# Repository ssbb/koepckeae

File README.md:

# koepckeae

koepckeae is a 34-key unibody split keyboard higihly inspired by Pete Johanson's [Zaphod Lite](https://gitlab.com/lpgalaxy/zaphod/-/tree/main), featuring hotswap support, splay, and spaced out thumbs.

## BOM

| Qty | Name                                                        | Source                                                                                                             |
|-----|-------------------------------------------------------------|--------------------------------------------------------------------------------------------------------------------|
| 1   | PCB                                                         | [gerbers](pcb/choc/koepckeae_gerbers.zip)                                                                          |
| 1   | XIAO nRF52840                                               | [Digikey](https://www.digikey.com/en/products/detail/seeed-technology-co-ltd/102010448/16652893)                   |
| 1   | 74HC595D shift register (SOIC-16)                           | [LCSC](https://www.lcsc.com/product-detail/Shifting-Register_Nexperia-74HC595D-118_C5947.html)                     |
| 1   | PCM12 power switch                                          | [LCSC](https://www.lcsc.com/product-detail/Slide-Switches_C-K-PCM12SMTR_C221841.html)                              |
| 1   | Panasonic EVQPUC02K reset button                            | [LCSC](https://www.lcsc.com/product-detail/_PANASONIC-_C79174.html)                                                |
| 2   | 1x1 Mill-Max Spring Loaded Header (0906-2-15-20-75-14-11-0) | [Digikey](https://www.digikey.com/en/products/detail/mill-max-manufacturing-corp/0906-2-15-20-75-14-11-0/1147050)  |
| 2   | 1x7 Mill-Max Header (310-43-107-41-001000)                  | [Digikey](https://www.digikey.com/en/products/detail/mill-max-manufacturing-corp/310-43-107-41-001000/1212181)     |
| 1   | JST PH-2.0 battery socket                                   | [LCSC](https://www.lcsc.com/product-detail/Wire-To-Board-Wire-To-Wire-Connector_JST-S2B-PH-K-S-LF-SN_C173752.html) |
| 1   | 702025 300 mAh battery                                      |                                                                                                                    |
| 34  | 1N4148W diode                                               | [LCSC](https://www.lcsc.com/product-detail/Switching-Diode_MDD-Microdiode-Electronics-1N4148W_C84367.html)         |
| 34  | Kailh Choc hotswap sockets                                  | [Aliexpress](https://aliexpress.com/item/33023283633.html?sku_id=10000000883911874)                                |

Max battery dimensions are 29mm x 21mm x 8mm. Ideally get a battery with JST connector but double check polarity on PCB.

### Plate case

| Qty | Name         | Source                                                             |
|-----|--------------|--------------------------------------------------------------------|
| 1   | Bottom Plate | [gerbers](mechanical/bottom-plate/bottom_plate_gerbers.zip)        |
| 8   | Solder Nuts  | [LCSC](https://www.lcsc.com/product-detail/_Sinhoo-_C2916384.html) |
| 8   | M2x5 screws  |                                                                    |

### Display

| Qty | Name                                                     | Source                                                                                                         |
|-----|----------------------------------------------------------|----------------------------------------------------------------------------------------------------------------|
| 1   | Adafruit Sharp Memory Display                            | [Adafruit](https://www.adafruit.com/product/3502)                                                              |
| 1   | 1x5 Mill-Max Spring Loaded Header (825-22-005-10-001101) | [Digikey](https://www.digikey.com/en/products/detail/mill-max-manufacturing-corp/825-22-005-10-001101/6149696) |
| 4   | M2.5x6 male-female nylon standoff                        | [Aliexpress](https://aliexpress.com/item/32871403400.html?sku_id=10000002420611426)                            |
| 4   | M2.5 nylon nut                                           | [Aliexpress](https://aliexpress.com/item/32868992270.html?sku_id=10000010058105677)                            |
| 4   | M2.5x6 nylon screw                                       | [Aliexpress](https://aliexpress.com/item/32870030598.html?sku_id=10000002668418327)                            |

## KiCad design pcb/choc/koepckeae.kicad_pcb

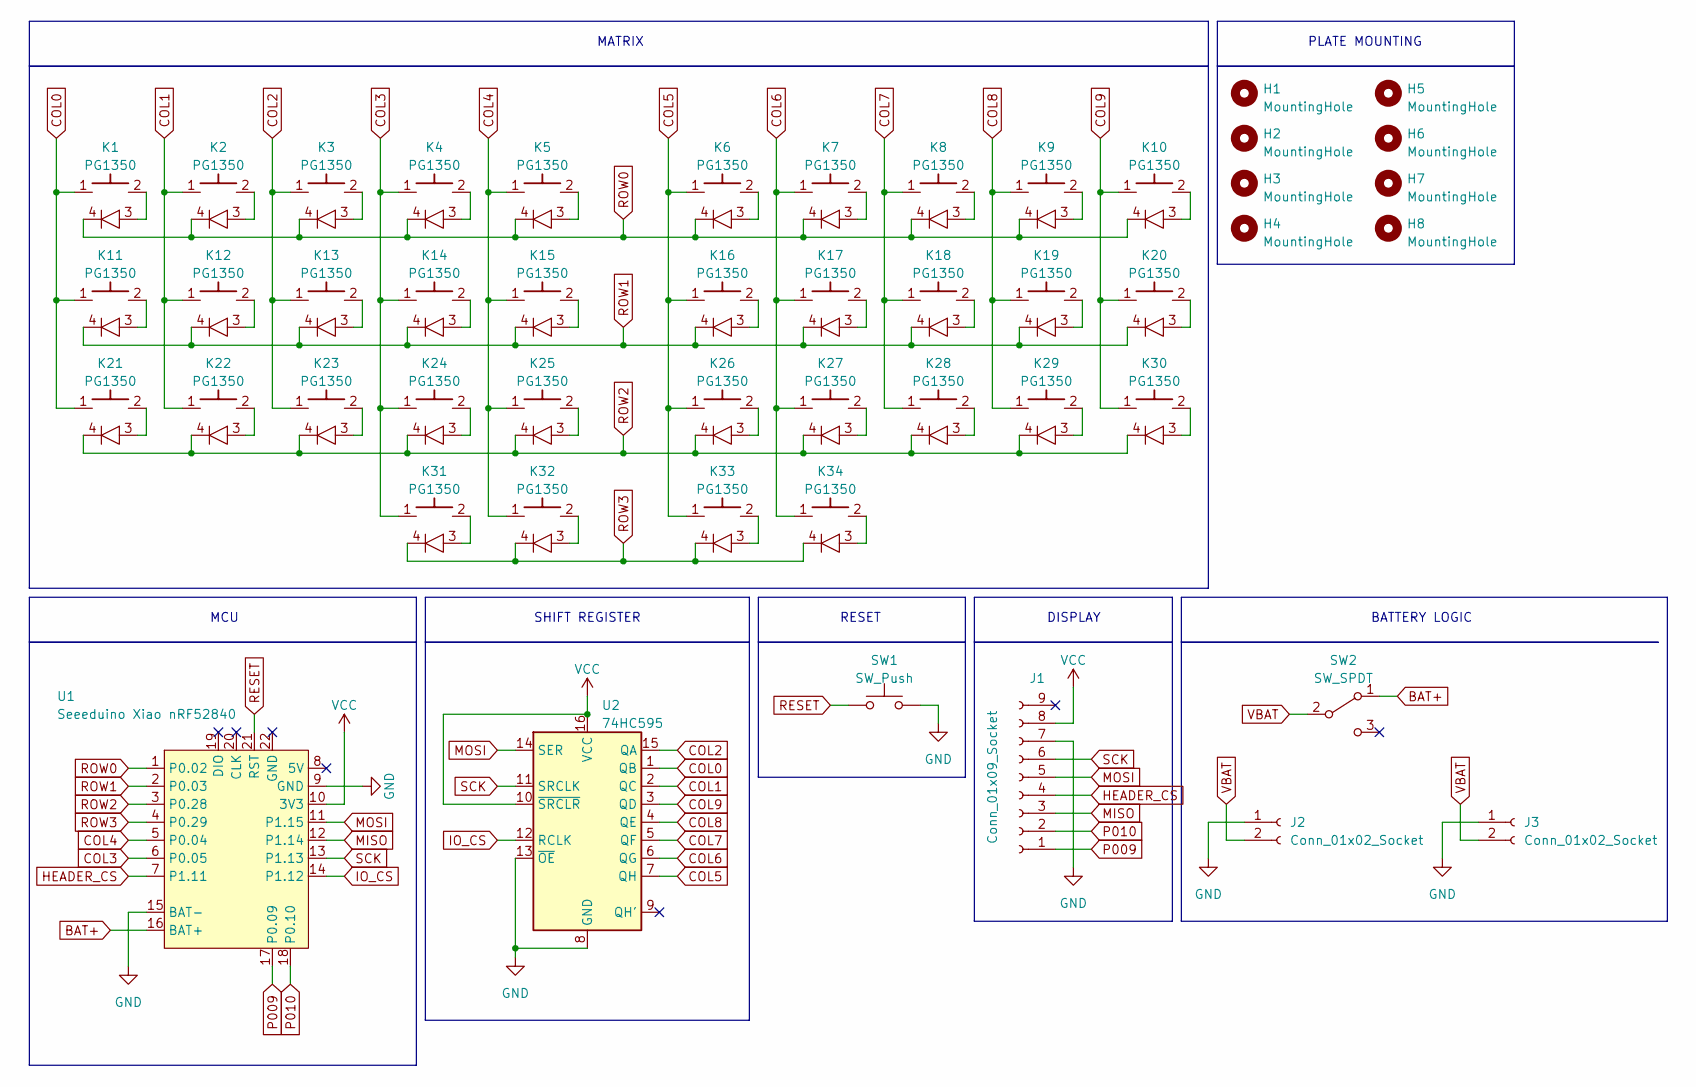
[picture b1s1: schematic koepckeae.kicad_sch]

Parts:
H1, H2, H3, H4, H5, H6, H7, H8: MountingHole
J1: Conn_01x09_Socket; Adafruit_Sharp_Memory_Display_1.3in
J2: Conn_01x02_Socket; PinHeader_1x02_P2.54mm_Vertical
J3: Conn_01x02_Socket; JST_PH_S2B-PH-K_1x02_P2.00mm_Horizontal
K1, K2, K3, K4, K5, K6, K7, K8, K9, K10, K11, K12, K13, K14, K15, K16, K17, K18, K19, K20, K21, K22, K23, K24, K25, K26, K27, K28, K29, K30, K31, K32, K33, K34: PG1350; PG1350_HS; LCSC C2099
SW1: SW_Push; Panasonic_EVQPUL_EVQPUC
SW2: SW_SPDT; SW_SPDT_PCM12
U1: Seeeduino Xiao nRF52840; Xiao_nRF52840_AH_Pogo
U2: 74HC595; SOIC-16_3.9x9.9mm_P1.27mm

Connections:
BAT+: SW2.1 (A), U1.16 (BAT+)
COL0: K1.1, K11.1, K21.1, U2.1 (QB)
COL1: K2.1, K12.1, K22.1, U2.2 (QC)
COL2: K3.1, K13.1, K23.1, U2.15 (QA)
COL3: K4.1, K14.1, K24.1, K31.1, U1.6 (P0.05)
COL4: K5.1, K15.1, K25.1, K32.1, U1.5 (P0.04)
COL5: K6.1, K16.1, K26.1, K33.1, U2.7 (QH)
COL6: K7.1, K17.1, K27.1, K34.1, U2.6 (QG)
COL7: K8.1, K18.1, K28.1, U2.5 (QF)
COL8: K9.1, K19.1, K29.1, U2.4 (QE)
COL9: K10.1, K20.1, K30.1, U2.3 (QD)
GND: J1.7, J2.1, J3.1, SW1.2, U1.9 (GND), U1.15 (BAT-), U2.8 (GND), U2.13 (~OE)
HEADER_CS: J1.4, U1.7 (P1.11)
IO_CS: U1.14 (P1.12), U2.12 (RCLK)
MISO: J1.3, U1.12 (P1.14)
MOSI: J1.5, U1.11 (P1.15), U2.14 (SER)
unnamed: K1.2, K1.3
unnamed: K2.2, K2.3
unnamed: K3.2, K3.3
unnamed: K4.2, K4.3
unnamed: K5.2, K5.3
unnamed: K6.2, K6.3
unnamed: K7.2, K7.3
unnamed: K8.2, K8.3
unnamed: K9.2, K9.3
unnamed: K10.2, K10.3
unnamed: K11.2, K11.3
unnamed: K12.2, K12.3
unnamed: K13.2, K13.3
unnamed: K14.2, K14.3
unnamed: K15.2, K15.3
unnamed: K16.2, K16.3
unnamed: K17.2, K17.3
unnamed: K18.2, K18.3
unnamed: K19.2, K19.3
unnamed: K20.2, K20.3
unnamed: K21.2, K21.3
unnamed: K22.2, K22.3
unnamed: K23.2, K23.3
unnamed: K24.2, K24.3
unnamed: K25.2, K25.3
unnamed: K26.2, K26.3
unnamed: K27.2, K27.3
unnamed: K28.2, K28.3
unnamed: K29.2, K29.3
unnamed: K30.2, K30.3
unnamed: K31.2, K31.3
unnamed: K32.2, K32.3
unnamed: K33.2, K33.3
unnamed: K34.2, K34.3
P009: J1.1, U1.17 (P0.09)
P010: J1.2, U1.18 (P0.10)
RESET: SW1.1, U1.21 (RST)
ROW0: K1.4, K2.4, K3.4, K4.4, K5.4, K6.4, K7.4, K8.4, K9.4, K10.4, U1.1 (P0.02)
ROW1: K11.4, K12.4, K13.4, K14.4, K15.4, K16.4, K17.4, K18.4, K19.4, K20.4, U1.2 (P0.03)
ROW2: K21.4, K22.4, K23.4, K24.4, K25.4, K26.4, K27.4, K28.4, K29.4, K30.4, U1.3 (P0.28)
ROW3: K31.4, K32.4, K33.4, K34.4, U1.4 (P0.29)
SCK: J1.6, U1.13 (P1.13), U2.11 (SRCLK)
VBAT: J2.2, J3.2, SW2.2 (B)
VCC: J1.8, U1.10 (3V3), U2.10 (~SRCLR), U2.16 (VCC)

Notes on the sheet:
MATRIX
SHIFT REGISTER
BATTERY LOGIC
PLATE MOUNTING
RESET
MCU
DISPLAY

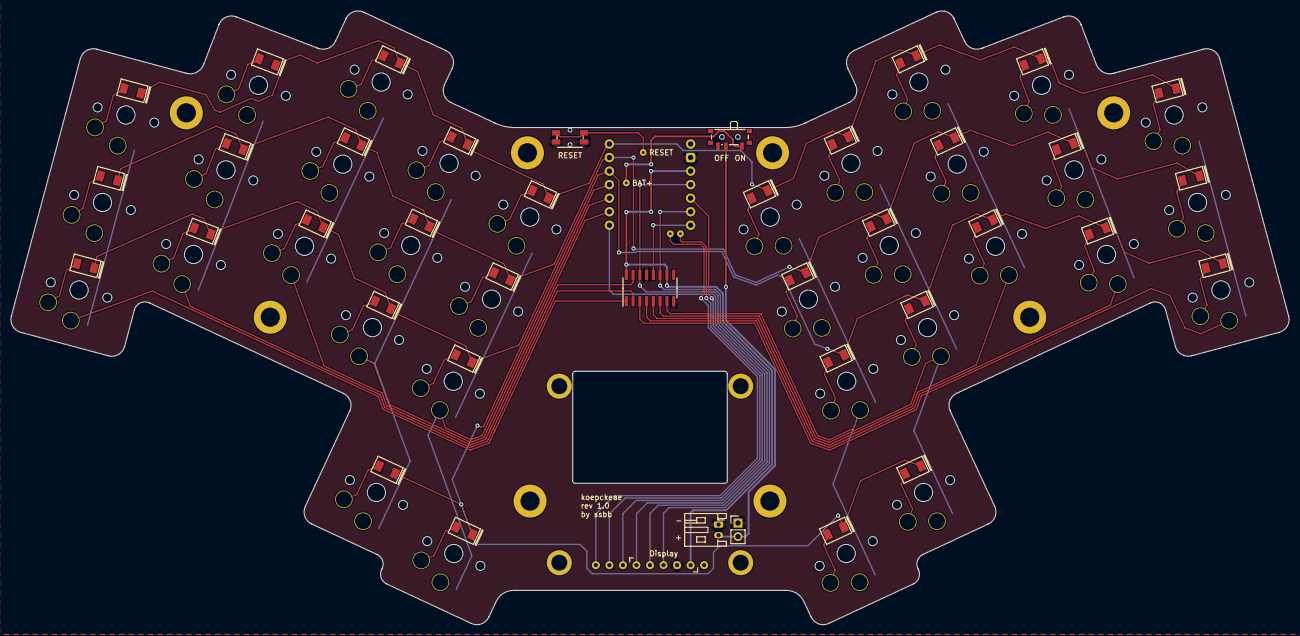
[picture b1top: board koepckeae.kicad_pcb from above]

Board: 2 copper layers, 239.8 x 115.1 mm, 49 parts (0 on the bottom side), 60 nets.

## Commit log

2023-11-04 Move kicad libs into its own dir
2023-11-04 Remove unused fpc
2023-11-04 Add bottom plate gerbers
2023-11-04 Add pcb gerbers
2023-11-04 Test if markdewon links to gerbers are working
2023-11-04 Add simple bom
2023-11-04 Update BOM
2023-11-04 add photo
2023-11-04 Remove u1 silk and re-generate gerbers
2023-11-04 Make bom a bit more obvious
2023-11-04 Improve BOM
2023-11-04 Update image and specify 595 package
2023-11-04 Add intro
2023-11-04 Fix intro
2023-11-05 Link xiao to digikey
2023-11-05 Add assembled photo
2023-11-05 Change image
2023-11-05 Change fsilk label
2023-11-06 Add experimental warning
2024-08-29 Remove obsolete warning
